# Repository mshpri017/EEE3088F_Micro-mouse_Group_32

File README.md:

# EEE3088F_Micro-mouse_Group_32
This repository contains the  documentation for the assembly of a micro mouse - a tiny robot that navigates mazes. Find PCB designs, assembly guides, and all the info you need to make your own micro mouse.  The repo contains PCB Designs, Gerber files and Bill of Materials (BOM) for the Power and Sensing subsystems

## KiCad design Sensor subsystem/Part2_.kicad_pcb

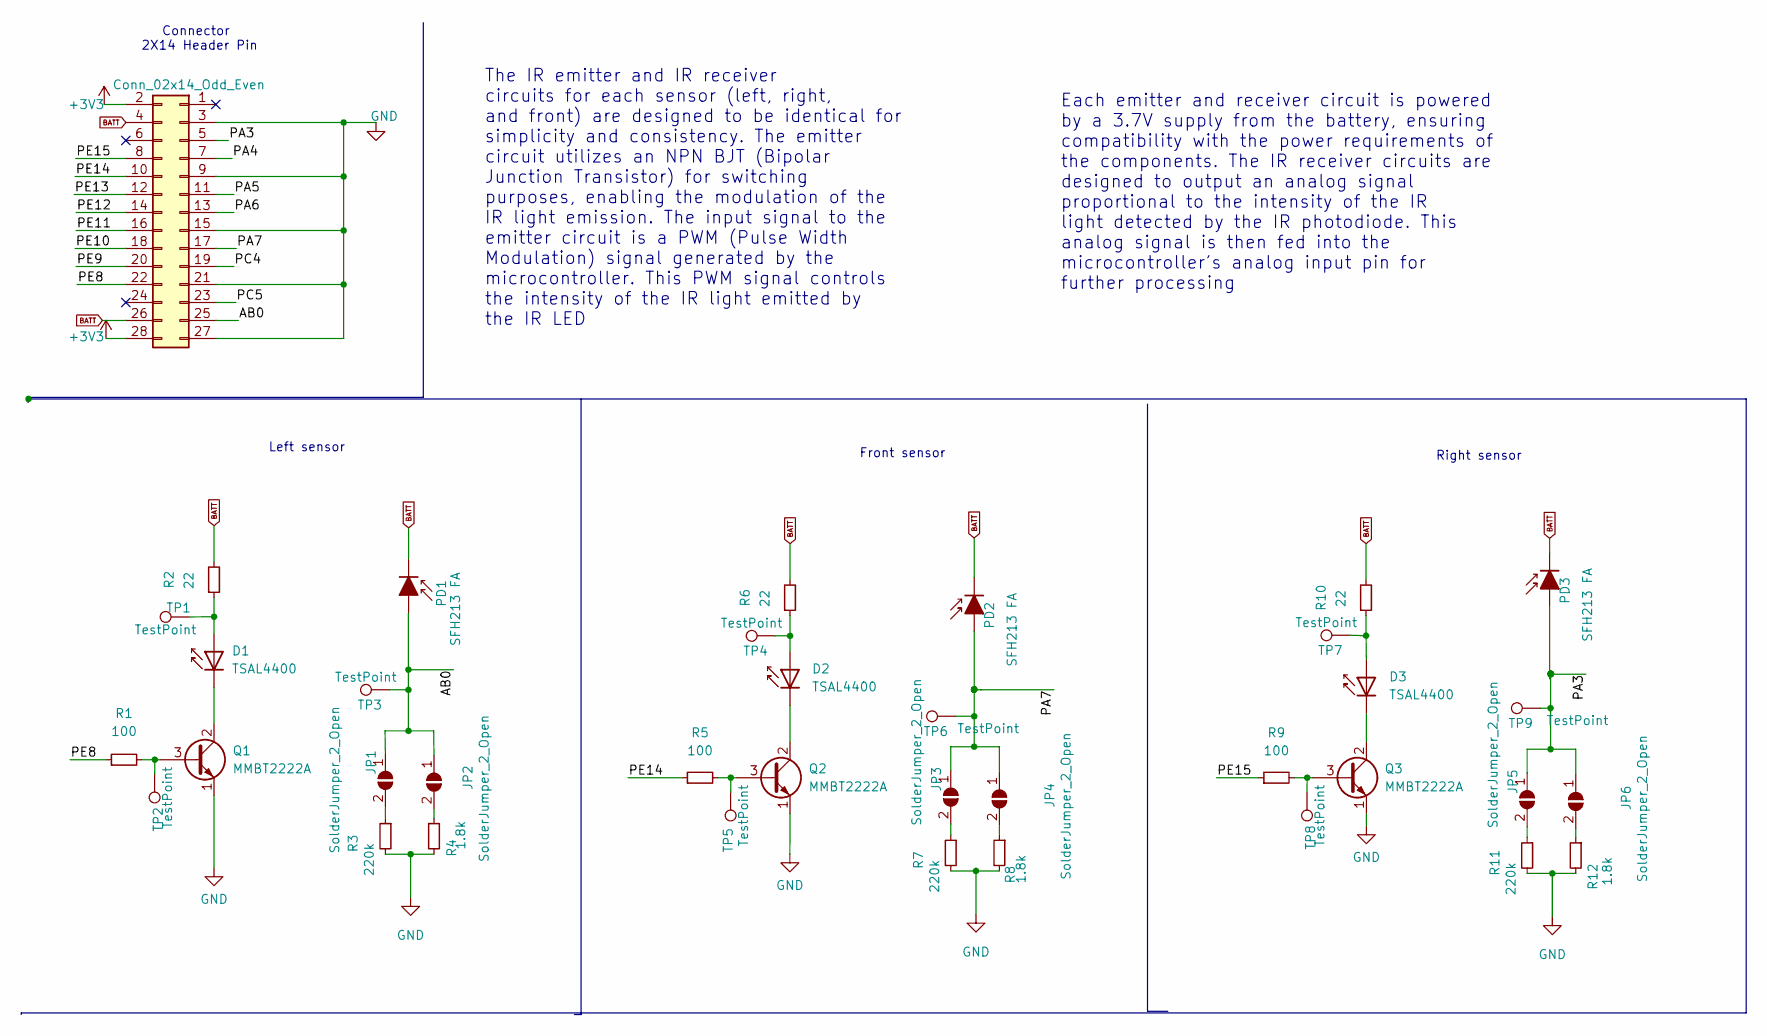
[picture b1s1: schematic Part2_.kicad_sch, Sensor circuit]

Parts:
D1, D2, D3: TSAL4400; LED_D3.0mm_Horizontal_O3.81mm_Z2.0mm
J1: Conn_02x14_Odd_Even; PinHeader_2x14_P2.54mm_Vertical
JP1, JP2, JP3, JP4, JP5, JP6: SolderJumper_2_Open; SolderJumper-2_P1.3mm_Open_TrianglePad1.0x1.5mm
PD1, PD2, PD3: SFH213 FA; XDCR_SFH_213_FA
Q1, Q2, Q3: MMBT2222A; TO-92_Inline
R1, R5, R9: 100; R_0805_2012Metric_Pad1.20x1.40mm_HandSolder
R2, R6, R10: 22; R_0805_2012Metric_Pad1.20x1.40mm_HandSolder
R3, R7, R11: 220k; R_0805_2012Metric_Pad1.20x1.40mm_HandSolder
R4, R8, R12: 1.8k; R_0805_2012Metric_Pad1.20x1.40mm_HandSolder
TP1, TP2, TP3, TP4, TP5, TP6, TP7, TP8, TP9: TestPoint; TestPoint_Pad_1.0x1.0mm

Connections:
+3V3: J1.2, J1.28
/AB0: J1.25, JP1.1 (A), JP2.1 (A), PD1.2 (A), TP3.1
/PA3: J1.5, JP5.1 (A), JP6.1 (A), PD3.2 (A), TP9.1
/PA4: J1.7
/PA5: J1.11
/PA6: J1.13
/PA7: J1.17, JP3.1 (A), JP4.1 (A), PD2.2 (A), TP6.1
/PC4: J1.19
/PC5: J1.23
/PE8: J1.22, R1.1
/PE9: J1.20
/PE10: J1.18
/PE11: J1.16
/PE12: J1.14
/PE13: J1.12
/PE14: J1.10, R5.1
/PE15: J1.8, R9.1
BATT: J1.4, J1.26, PD1.1 (K), PD2.1 (K), PD3.1 (K), R2.2, R6.2, R10.2
GND: J1.3, J1.9, J1.15, J1.21, J1.27, Q1.1 (E), Q2.1 (E), Q3.1 (E), R3.2, R4.2, R7.2, R8.2, R11.2, R12.2
unnamed: D1.1 (K), Q1.2 (C)
unnamed: D1.2 (A), R2.1, TP1.1
unnamed: D2.1 (K), Q2.2 (C)
unnamed: D2.2 (A), R6.1, TP4.1
unnamed: D3.1 (K), Q3.2 (C)
unnamed: D3.2 (A), R10.1, TP7.1
unnamed: JP1.2 (B), R3.1
unnamed: JP2.2 (B), R4.1
unnamed: JP3.2 (B), R7.1
unnamed: JP4.2 (B), R8.1
unnamed: JP5.2 (B), R11.1
unnamed: JP6.2 (B), R12.1
unnamed: Q1.3 (B), R1.2, TP2.1
unnamed: Q2.3 (B), R5.2, TP5.1
unnamed: Q3.3 (B), R9.2, TP8.1

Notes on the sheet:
Connector 2X14 Header Pin
Left sensor
Right sensor
The IR emitter and IR receiver circuits for each sensor (left, right, and front) are designed to be identical for simplicity and consistency. The emitter circuit utilizes an NPN BJT (Bipolar Junction Transistor) for switching purposes, enabling the modulation of the IR light emission. The input sig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
Each emitter and receiver circuit is powered by a 3.7V supply from the battery, ensuring compatibility with the power requirements of the components. The IR receiver circuits are designed to output an analog signal proportional to the intensity of the IR light detected by the IR photodiode. This an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
Front sensor

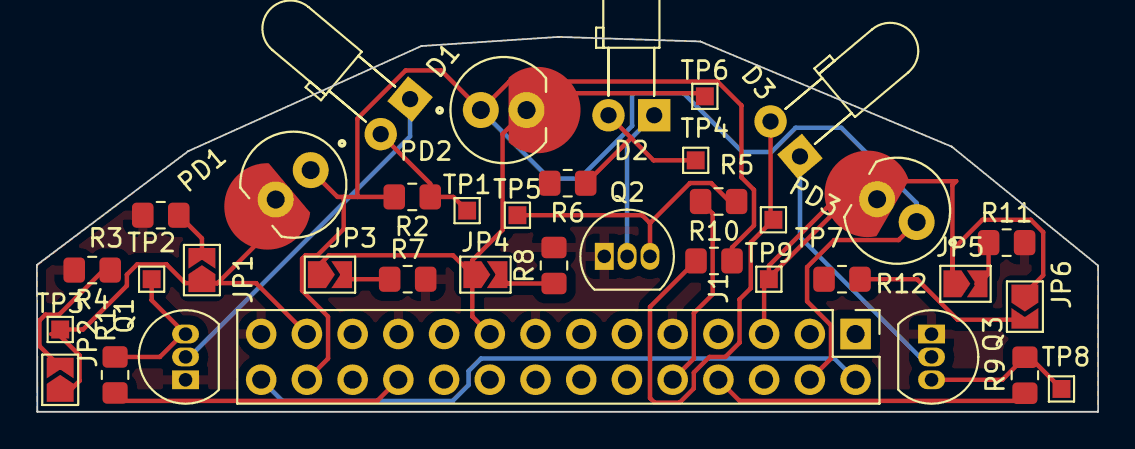
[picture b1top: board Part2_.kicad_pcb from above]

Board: 2 copper layers, 59.0 x 20.8 mm, 37 parts (0 on the bottom side), 24 nets.

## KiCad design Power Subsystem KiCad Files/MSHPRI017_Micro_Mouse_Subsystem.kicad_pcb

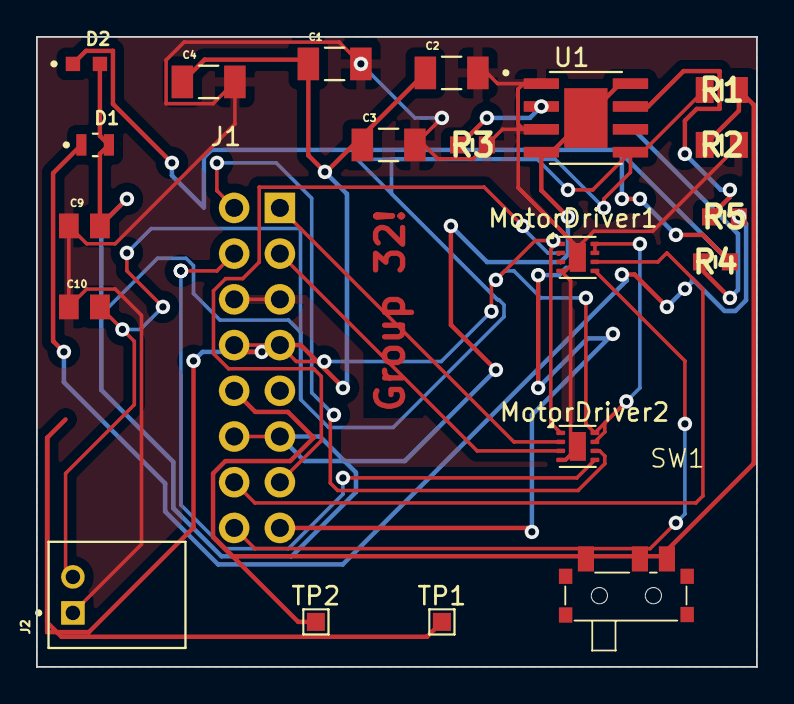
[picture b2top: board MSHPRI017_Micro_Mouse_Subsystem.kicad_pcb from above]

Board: 2 copper layers, 40.0 x 35.0 mm, 21 parts (1 on the bottom side), 18 nets.

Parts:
C1, C2, C3, C4: CL31B104KBCNNNC; CAPC3216X180N
C9, C10: CL21A106KAYNNNE; CAPC2012X135N
D1: KT-0805W; LED_KT-0805W
D2: KT-0603R; LED_KT-0603R
J1: Conn_02x08_Odd_Even; PinHeader_2x08_P2.54mm_Vertical
J2: S2B-PH-K-S_LF__SN_; JST_S2B-PH-K-S_LF__SN_
MotorDriver1, MotorDriver2: DRV8837; WSON-8-1EP_2x2mm_P0.5mm_EP0.9x1.6mm
R1, R2: 0805W8F1003T5E; RESC2013X65N
R3: 0603WAF7501T5E; RESC1608X55N
R4, R5: 0603WAF1001T5E; RESC1608X55N
SW1: SW_SPDT; mySwitch
TP1, TP2: TestPoint; TestPoint_Pad_1.0x1.0mm
U1: TP4056; SOP127P600X175-9N

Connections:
5V_uC: C9.2, D1.A, D2.A, J1.11, J1.12, U1.4 (VCC), U1.8 (CE), U1.9 (EP)
Bat+: C10.2, J2.2, R1.1, SW1.1 (A), U1.5 (BAT)
Bat-: C1.2, C2.2, C3.2, C4.2, C9.1, C10.1, J1.5, J1.6, J2.1, MotorDriver1.4 (GND), MotorDriver1.9 (GND), MotorDriver2.4 (GND), MotorDriver2.9 (GND), R2.2, R3.2, U1.1 (TEMP), U1.3 (GND)
Batt: C1.1, C2.1, C3.1, C4.1, J1.7, J1.8, MotorDriver1.1 (VM), MotorDriver1.7 (~SLEEP), MotorDriver1.8 (VCC), MotorDriver2.1 (VM), MotorDriver2.7 (~SLEEP), MotorDriver2.8 (VCC), SW1.2 (B), TP1.1
Motor1_A: J1.13, MotorDriver1.2 (OUT1)
Motor1_B: J1.15, MotorDriver1.3 (OUT2)
Motor2_A: J1.1, MotorDriver2.2 (OUT1)
Motor2_B: J1.3, MotorDriver2.3 (OUT2)
unnamed: D1.C, R5.2
unnamed: D2.C, R4.2
unnamed: R3.1, U1.2 (PROG)
unnamed: R5.1, U1.7 (~CHRG)
unnamed: R4.1, U1.6 (~STDBY)
PWM1_A: J1.14, MotorDriver1.6 (IN1)
PWM1_B: J1.16, MotorDriver1.5 (IN2)
PWM2_A: J1.2, MotorDriver2.6 (IN1)
PWM2_B: J1.4, MotorDriver2.5 (IN2)
V_ADC: J1.10, R1.2, R2.1, TP2.1

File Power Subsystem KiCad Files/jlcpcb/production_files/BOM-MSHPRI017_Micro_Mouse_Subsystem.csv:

Comment,Designator,Footprint,LCSC
0805W8F1003T5E,"R1,R2",RESC2013X65N,C149504
CL21A106KAYNNNE,"C10,C9",CAPC2012X135N,C15850
0603WAF1001T5E,"R4,R5",RESC1608X55N,C21190
KT-0603R,D2,LED_KT-0603R,C2286
0603WAF7501T5E,R3,RESC1608X55N,C23234
CL31B104KBCNNNC,"C1,C2,C3,C4",CAPC3216X180N,C24497
SW_SPDT,SW1,mySwitch,C2890358
KT-0805W,D1,LED_KT-0805W,C34499
DRV8837,"MotorDriver1,MotorDriver2",WSON-8-1EP_2x2mm_P0.5mm_EP0.9x1.6mm,C39159
TP4056,U1,SOP127P600X175-9N,C725790
S2B-PH-K-S_LF__SN_,J2,JST_S2B-PH-K-S_LF__SN_,
